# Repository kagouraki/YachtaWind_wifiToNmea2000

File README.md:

# YachtaWind_wifiToNmea2000
esp32 Wifi to Nmea2000 converter

This board and firmware is just a nmea2000 converter. It converts and sends all nmea183 it recieves from a wifi tcp server to the wired Nmea2000 devices. It is powered from the NMEA2000 network
At some point i will write a guide how to use it and understand the leds.  Until then if you have questions open a discussion. 
It is build to recieve the nmea stream from original Norbert Walter's yachta wind sensor project. 
I made some minor modifications to the pcb, 3dprinted parts and software. You can find everything in my gitlab repos.

Thank you

G.

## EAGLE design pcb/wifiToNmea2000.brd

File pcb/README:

These are the pcb files.
I ordered the board with this exact gerber files from jlcpcb. Just upload the .zip file to the jlcpcb website.

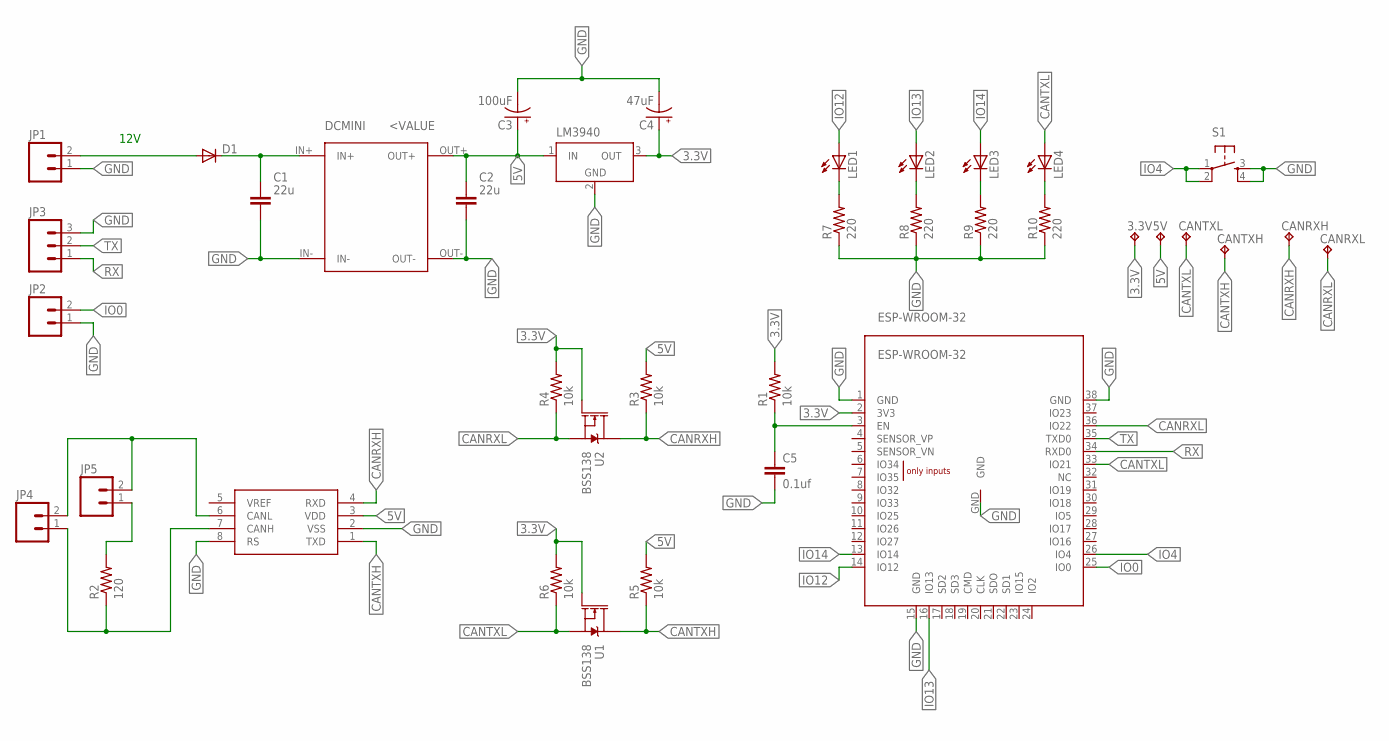
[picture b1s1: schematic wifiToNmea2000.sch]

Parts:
3.3V, 5V: TPTP20R; TP20R
C1, C2: 22u; C1206
C3: 100uF; PANASONIC_D
C4: 47uF; PANASONIC_D
C5: 0.1uf; 0805
CANRXH: TPTP20R; TP20R
CANRXL: TPTP20R; TP20R
CANTXH: TPTP20R; TP20R
CANTXL: TPTP20R; TP20R
D1: DIODE-DO214AC; DO214AC
DCMINI: DCDCMINI
ESP-WROOM-32: ESP-WROOM-32
JP1, JP4: M02; 1X02_LONGPADS
JP2, JP5: M02LOCK; 1X02_LOCK
JP3: M03LOCK; 1X03_LOCK
LED1, LED2, LED3, LED4: LED3MM
LM3940: LT1129CST5; SOT223
MCP2551: MCP2551; SO08
R1, R3, R4, R5, R6: 10k; 0805
R2: 120; 0805
R7, R8, R9, R10: 220; 0805
S1: TAC_SWITCHPTH; TACTILE-PTH
U1, U2: BSS138; SOT65P210X110-3N

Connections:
3.3V: 3.3V.TP, C4.+, ESP-WROOM-32.2 (3V3), LM3940.3 (OUT), R1.2, R4.2, R6.2, U1.1 (G), U2.1 (G)
5V: 5V.TP, C2.1, C3.+, DCMINI.OUT+, LM3940.1 (IN), MCP2551.3 (VDD), R3.2, R5.2
CANRXH: CANRXH.TP, MCP2551.4 (RXD), R3.1, U2.3 (D)
CANRXL: CANRXL.TP, ESP-WROOM-32.36 (IO22), R4.1, U2.2 (S)
CANTXH: CANTXH.TP, MCP2551.1 (TXD), R5.1, U1.3 (D)
CANTXL: CANTXL.TP, ESP-WROOM-32.33 (IO21), LED4.A, R6.1, U1.2 (S)
GND: C1.2, C2.2, C3.-, C4.-, C5.2, DCMINI.IN-, DCMINI.OUT-, ESP-WROOM-32.1 (GND), ESP-WROOM-32.15 (GND), ESP-WROOM-32.38 (GND), ESP-WROOM-32.GND, JP1.1, JP2.1, JP3.3, LM3940.2 (GND), LM3940.4 (GND), MCP2551.2 (VSS), MCP2551.8 (RS), R7.1, R8.1, R9.1, R10.1, S1.3, S1.4
IO0: ESP-WROOM-32.25 (IO0), JP2.2
IO4: ESP-WROOM-32.26 (IO4), S1.1, S1.2
IO12: ESP-WROOM-32.14 (IO12), LED1.A
IO13: ESP-WROOM-32.16 (IO13), LED2.A
IO14: ESP-WROOM-32.13 (IO14), LED3.A
unnamed: D1.A, JP1.2
unnamed: C1.1, D1.C, DCMINI.IN+
unnamed: JP4.1, MCP2551.7 (CANH), R2.1
unnamed: JP4.2, JP5.2, MCP2551.6 (CANL)
unnamed: C5.1, ESP-WROOM-32.3 (EN), R1.1
unnamed: JP5.1, R2.2
unnamed: LED1.K (C), R7.2
unnamed: LED2.K (C), R8.2
unnamed: LED3.K (C), R9.2
unnamed: LED4.K (C), R10.2
RX: ESP-WROOM-32.34 (RXD0), JP3.1
TX: ESP-WROOM-32.35 (TXD0), JP3.2

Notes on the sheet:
12V

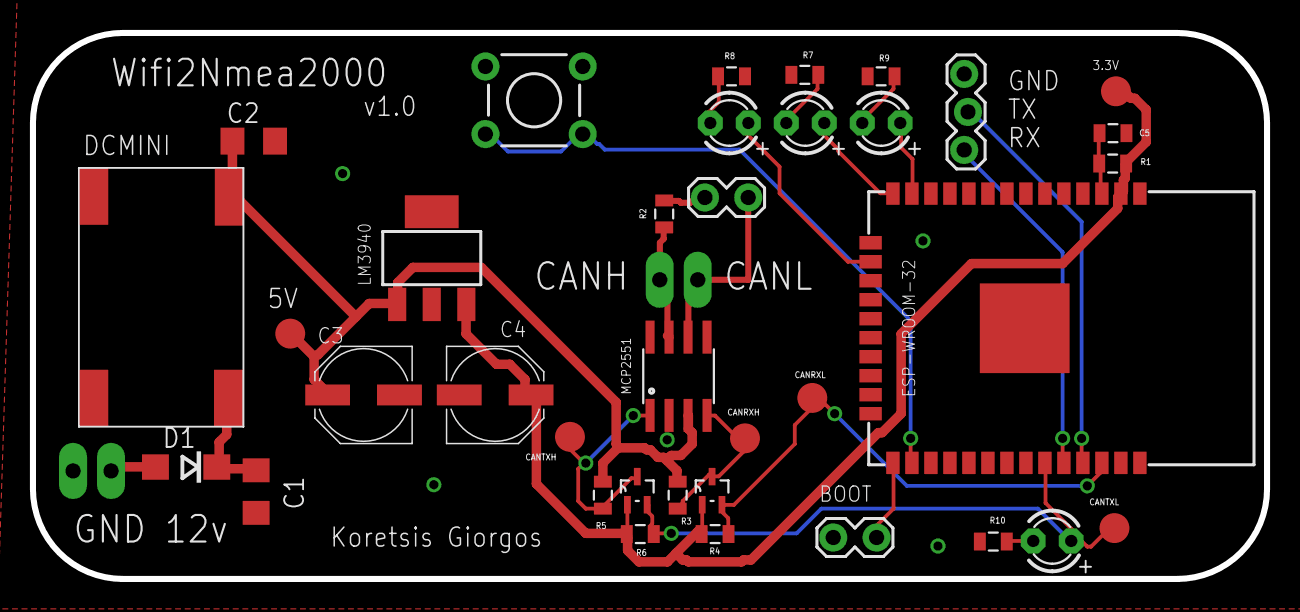
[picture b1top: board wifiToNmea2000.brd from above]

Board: 2 copper layers, 82.5 x 36.5 mm, 38 parts (0 on the bottom side), 24 nets.
